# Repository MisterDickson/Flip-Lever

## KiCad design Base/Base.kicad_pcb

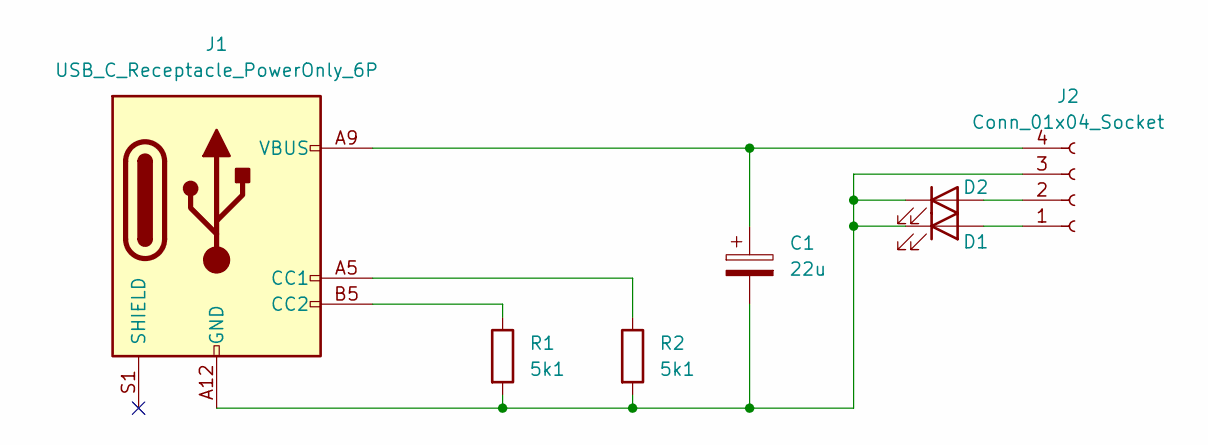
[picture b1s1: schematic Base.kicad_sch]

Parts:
C1: 22u; CP_Radial_D5.0mm_P2.50mm
D1, D2: LED; LED_D5.0mm_Clear
J1: USB_C_Receptacle_PowerOnly_6P; USB_C_Receptacle_GCT_USB4135-GF-A_6P_TopMnt_Horizontal
J2: Conn_01x04_Socket; PinSocket_1x04_P2.54mm_Vertical
R1, R2: 5k1; R_Axial_DIN0207_L6.3mm_D2.5mm_P10.16mm_Horizontal

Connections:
unnamed: D1.2 (A), J2.1
unnamed: C1.2, D1.1 (K), D2.1 (K), J1.A12 (GND), J1.B12 (GND), J2.3, R1.2, R2.2
unnamed: D2.2 (A), J2.2
unnamed: J1.A5 (CC1), R2.1
unnamed: J1.B5 (CC2), R1.1
unnamed: C1.1, J1.A9 (VBUS), J1.B9 (VBUS), J2.4

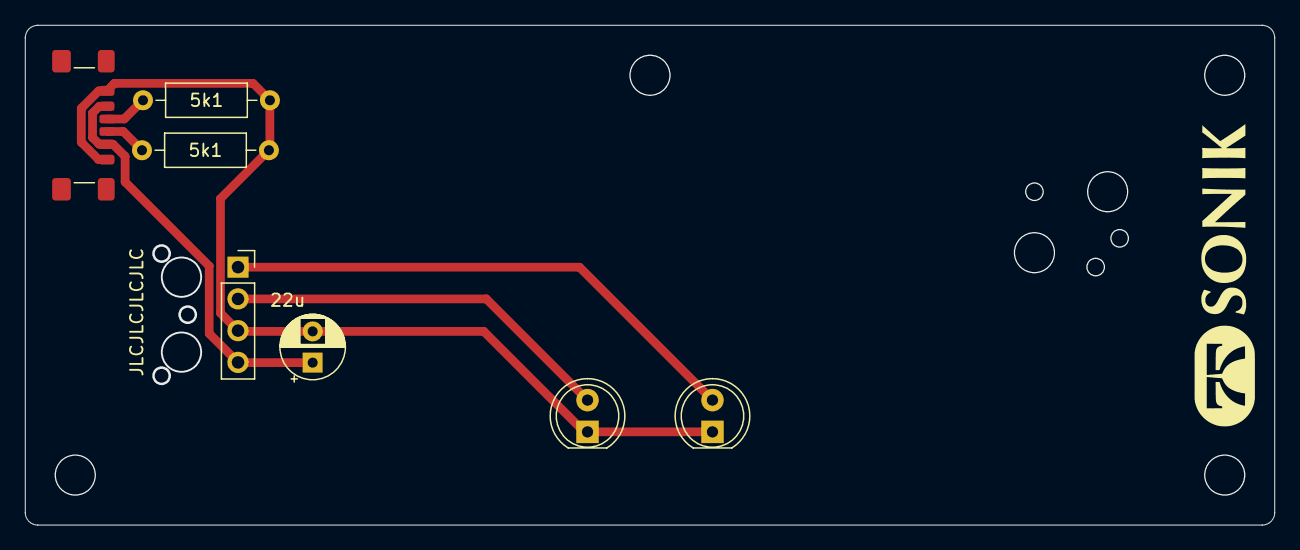
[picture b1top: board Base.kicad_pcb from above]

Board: 2 copper layers, 100.0 x 40.0 mm, 7 parts (0 on the bottom side), 6 nets.

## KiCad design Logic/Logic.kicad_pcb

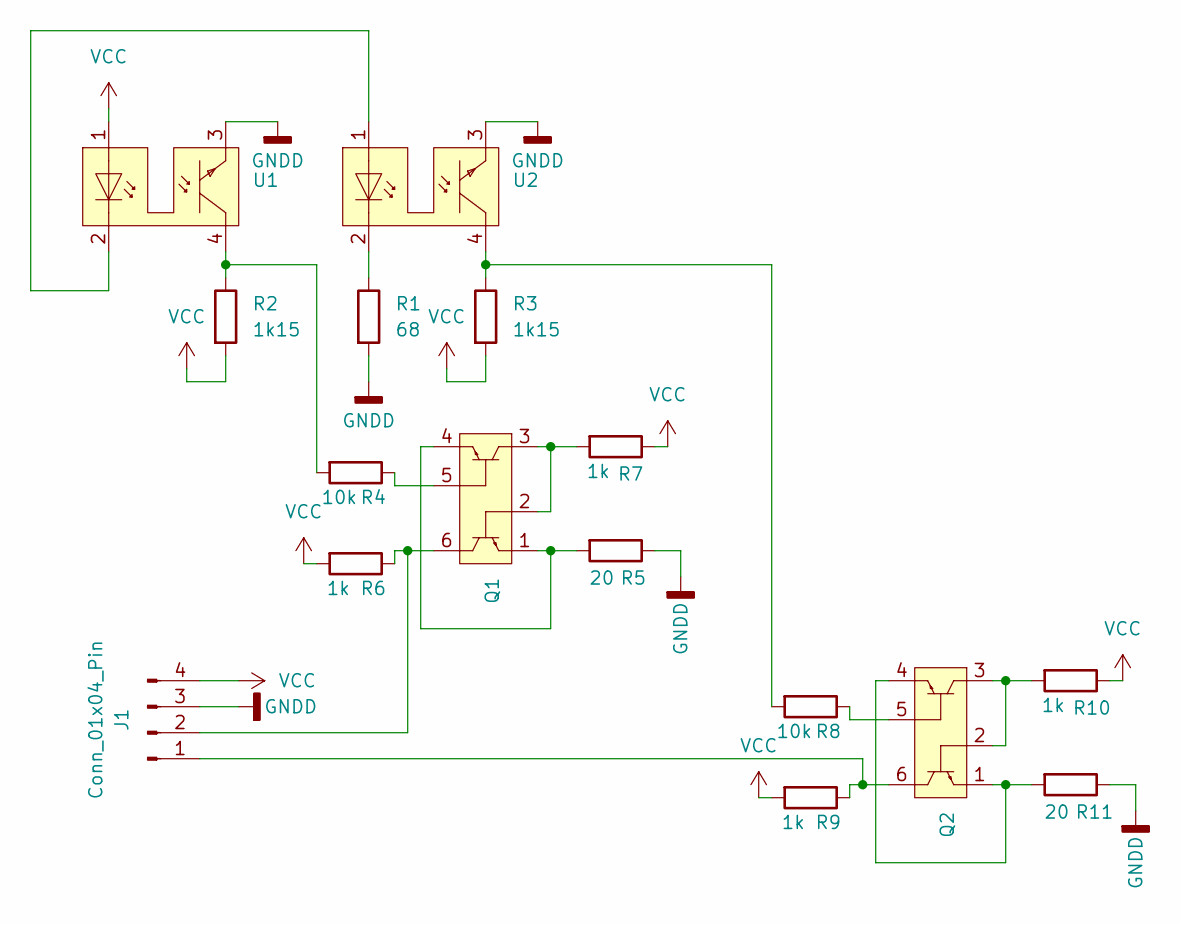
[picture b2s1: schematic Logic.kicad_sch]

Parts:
J1: Conn_01x04_Pin; Harwin_M20-89004xx_1x04_P2.54mm_Horizontal
Q1, Q2: SOT-363_SC-70-6
R1: 68; R_0603_1608Metric_Pad0.98x0.95mm_HandSolder
R2, R3: 1k15; R_0603_1608Metric_Pad0.98x0.95mm_HandSolder
R4, R8: 10k; R_0603_1608Metric_Pad0.98x0.95mm_HandSolder
R5, R11: 20; R_0603_1608Metric_Pad0.98x0.95mm_HandSolder
R6, R7, R9, R10: 1k; R_0603_1608Metric_Pad0.98x0.95mm_HandSolder
U1, U2: OPTO-THT-TCST1103

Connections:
GNDD: J1.3, R1.2, R5.1, R11.1, U1.3, U2.3
unnamed: J1.1, Q2.6, R9.1
unnamed: J1.2, Q1.6, R6.1
unnamed: Q1.1, Q1.4, R5.2
unnamed: Q1.2, Q1.3, R7.2
unnamed: Q1.5, R4.1
unnamed: Q2.1, Q2.4, R11.2
unnamed: Q2.2, Q2.3, R10.2
unnamed: Q2.5, R8.1
unnamed: R1.1, U2.2
unnamed: R2.1, R4.2, U1.4
unnamed: R3.1, R8.2, U2.4
unnamed: U1.2, U2.1
VCC: J1.4, R2.2, R3.2, R6.2, R7.1, R9.2, R10.1, U1.1

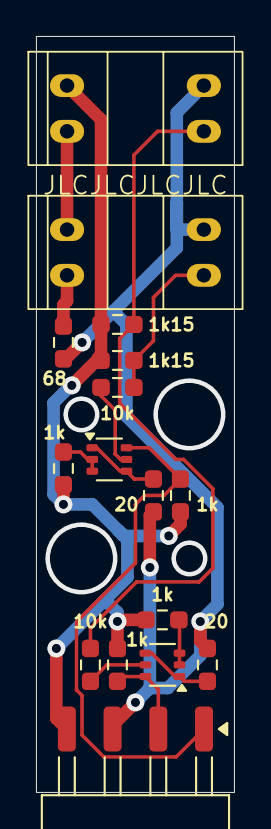
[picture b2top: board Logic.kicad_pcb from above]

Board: 2 copper layers, 11.0 x 42.0 mm, 16 parts (0 on the bottom side), 14 nets.

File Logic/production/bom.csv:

Designator,Footprint,Quantity,Value,LCSC Part #
J1,Harwin_M20-89004xx_1x04_P2.54mm_Horizontal,1,Conn_01x04_Pin,
"Q1, Q2",SOT-363_SC-70-6,2,~,
R1,0603,1,68,
"R10, R6, R7, R9",0603,4,1k,
"R11, R5",0603,2,20,
"R2, R3",0603,2,1k15,
"R4, R8",0603,2,10k,
"U1, U2",OPTO-THT-TCST1103,2,~,

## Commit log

2025-05-04 init
2025-05-04 Add Schmitt-Trigger and Datasheets
2025-05-05 user save
2025-05-05 user saved
2025-05-05 init base
2025-05-05 schematic update
2025-05-05 add drawings
2025-05-05 quick save
2025-05-05 add components
2025-05-05 update pcb
2025-05-05 RC2
    add fab s/n placeholder
2025-05-05 RC2, un-ground shield
2025-05-05 color update
2025-05-05 add production files
2025-05-06 add BOM
2025-05-06 flip drawing
2025-05-22 update drill holes
    notified by jlc about the fab capabilities. 3.1 to 3 mm, 1.3 to 1.1 mm. tested. works. even better
2025-06-01 First order
2025-06-01 flip
2025-06-01 re-structure
